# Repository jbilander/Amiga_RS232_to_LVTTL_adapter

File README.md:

# Amiga RS232 to LVTTL adapter

Amiga RS232 to LVTTL with 3.3V Power converted and taken directly from the DB25 serial port 12V-pin (pin 9)

***
VERIFIED WORKING!!!<br />
https://drive.google.com/file/d/105Ov4MyicygtOqv-1FFOkmMn0a-dk8-Z/view?usp=sharing
***

Revision 1A
<br />

<br />

<br />

<br />

BOM Rev. 1A
---------
Designator  | Name/Value   | Package | Notes
-|-|-|-|
U1 | TPS54308 Step-down converter | SOT-23-6 | [TPS54308DDCR](https://www.mouser.com/ProductDetail/595-TPS54308DDCR)
U2 | MAX3232 RS-232 Interface IC 3-5.5V | TSSOP-16 | [MAX3232IPWR](https://www.mouser.com/ProductDetail/595-MAX3232IPWR)
L1 | CLF7045NIT-100M-D Power Inductor, 10 uH | 7 mm x 7 mm, height 4.5 mm | [CLF7045NIT](https://www.mouser.com/ProductDetail/810-CLF7045NIT100MD)
J1 | D-Sub DB25 Female connector | EdgeMount, serial port connector solder type | [D-Sub DB25F](https://www.aliexpress.com/item/32885764031.html)
J2 | 1x05 Right-Angle Single Row Male Pin Header | Type/Color: Reverse | [PinHeader](https://www.aliexpress.com/item/32892547934.html)
R1 | Feedback Resistor 22k Ω | 0603 | [RC0603FR-0722KL](https://www.mouser.com/ProductDetail/603-RC0603FR-0722KL)
R2 | Feedback Resistor 100k Ω | 0603 | [RC0603FR-07100KL](https://www.mouser.com/ProductDetail/603-RC0603FR-07100KL) 
R3-R5 | LED Resistor 1k Ω | 0603 | [RC0603FR-071KL](https://www.mouser.com/ProductDetail/603-RC0603FR-071KL)
C1 | Capacitor 10uF | 0805 | [TMK212BBJ106KG-T](https://www.mouser.com/ProductDetail/963-TMK212BBJ106KG-T)
C2,C4 | Capacitor 0.1uF = 100nF | 0805 |
C3 | Capacitor 47uF | 1206 | [EMK316BBJ476ML-T](https://www.mouser.com/ProductDetail/963-EMK316BBJ476ML-T)
C5-C8 | Capacitor 0.1uF = 100nF | 0603 | [CL10B104KO8NNWC](https://www.mouser.com/ProductDetail/187-CL10B104KO8NNWC)
D1-D3 | SMD LED | 0603 | [SMD LED 0603](https://www.aliexpress.com/item/1005003836509392.html)

***

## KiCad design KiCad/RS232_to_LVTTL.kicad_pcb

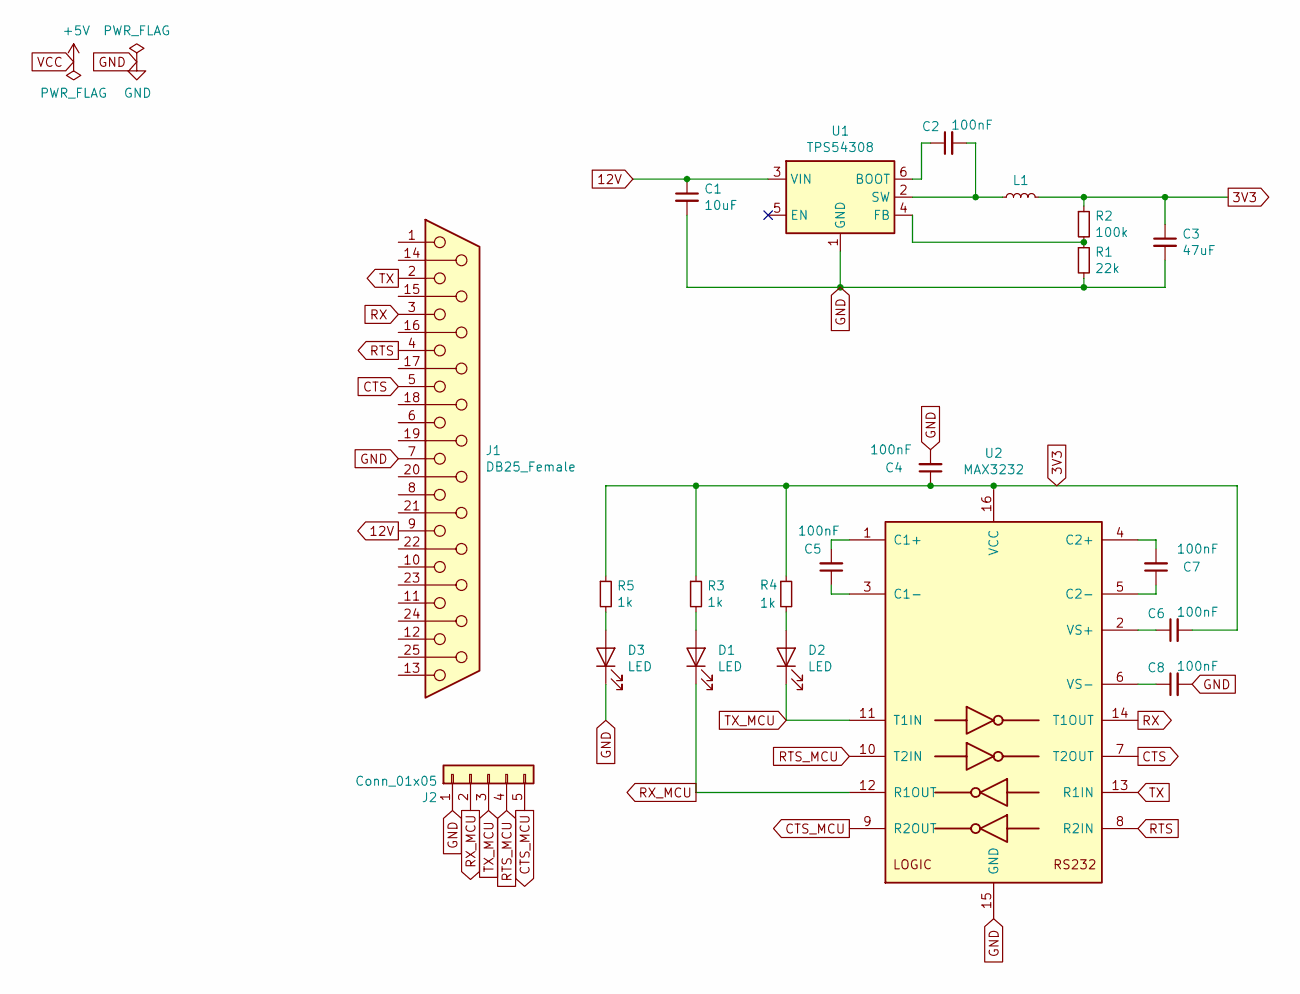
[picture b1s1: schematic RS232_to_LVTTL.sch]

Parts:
C1: 10uF; C_0805_2012Metric_Pad1.15x1.40mm_HandSolder
C2, C4: 100nF; C_0805_2012Metric_Pad1.15x1.40mm_HandSolder
C3: 47uF; C_1206_3216Metric_Pad1.42x1.75mm_HandSolder
C5, C6, C7, C8: 100nF; C_0603_1608Metric_Pad1.05x0.95mm_HandSolder
D1, D2, D3: LED; D_0603_1608Metric_Pad1.05x0.95mm_HandSolder
J1: DB25_Female; DSUB-25_Female_EdgeMount_P2.77mm
J2: Conn_01x05; PinHeader_1x05_P2.54mm_Vertical
L1: L_Small; L_Wuerth_HCM-7050
R1: 22k; R_0603_1608Metric_Pad1.05x0.95mm_HandSolder
R2: 100k; R_0603_1608Metric_Pad1.05x0.95mm_HandSolder
R3, R4, R5: 1k; R_0603_1608Metric_Pad1.05x0.95mm_HandSolder
U1: TPS54308; SOT-23-6
U2: MAX3232; TSSOP-16_4.4x5mm_P0.65mm

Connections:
3V3: C3.1, C4.1, C6.2, L1.2, R2.1, R3.1, R4.1, R5.1, U2.16 (VCC)
12V: C1.1, J1.9, U1.3 (VIN)
CTS: J1.5, U2.7 (T2OUT)
CTS_MCU: J2.5, U2.9 (R2OUT)
GND: C1.2, C3.2, C4.2, C8.2, D3.1 (K), J1.7, J2.1, R1.2, U1.1 (GND), U2.15 (GND)
unnamed: C2.1, U1.6 (BOOT)
unnamed: C2.2, L1.1, U1.2 (SW)
unnamed: C5.1, U2.3 (C1-)
unnamed: C5.2, U2.1 (C1+)
unnamed: C6.1, U2.2 (VS+)
unnamed: C7.1, U2.5 (C2-)
unnamed: C7.2, U2.4 (C2+)
unnamed: C8.1, U2.6 (VS-)
unnamed: D1.2 (A), R3.2
unnamed: D2.2 (A), R4.2
unnamed: D3.2 (A), R5.2
unnamed: R1.1, R2.2, U1.4 (FB)
RTS: J1.4, U2.8 (R2IN)
RTS_MCU: J2.4, U2.10 (T2IN)
RX: J1.3, U2.14 (T1OUT)
RX_MCU: D1.1 (K), J2.2, U2.12 (R1OUT)
TX: J1.2, U2.13 (R1IN)
TX_MCU: D2.1 (K), J2.3, U2.11 (T1IN)

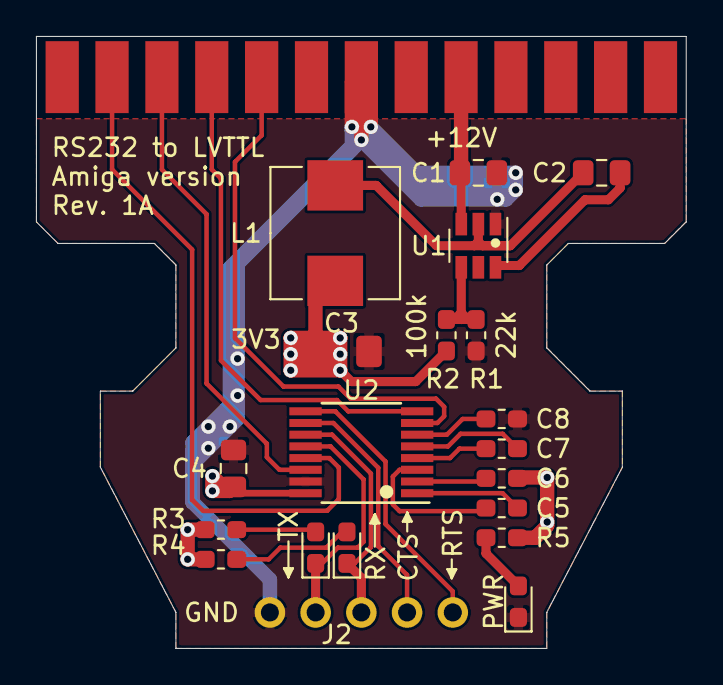
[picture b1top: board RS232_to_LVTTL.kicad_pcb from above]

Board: 2 copper layers, 36.1 x 34.0 mm, 21 parts (0 on the bottom side), 23 nets.

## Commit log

2023-03-30 Create LICENSE
2023-03-30 Added KiCAD-files
2023-03-31 Added power circuit convert 12V to 3.3V
2023-03-31 Added MAX3232 chip
2023-03-31 Added 5-pin header for TX,RX,RTS,CTS,GND
2023-03-31 Fixed positioning of 5-pin header
2023-04-01 routing and placing of components
2023-04-01 Added a PWR LED and some final routing and silkscreen fixes
2023-04-01 Added screenshot pics
2023-04-02 Added screenshot pic
2023-04-02 some small routing and silkscreen fixes
2023-04-02 replaced with new screenshot pics
2023-04-02 small fix in schematic
2023-04-02 Added schematic pdf
2023-04-11 Moved the Inductor a little to the right to get further away from the signal traces
2023-04-11 Updated screenshots
2023-04-17 moved schematic pdf up one level
2023-04-30 Added pics
